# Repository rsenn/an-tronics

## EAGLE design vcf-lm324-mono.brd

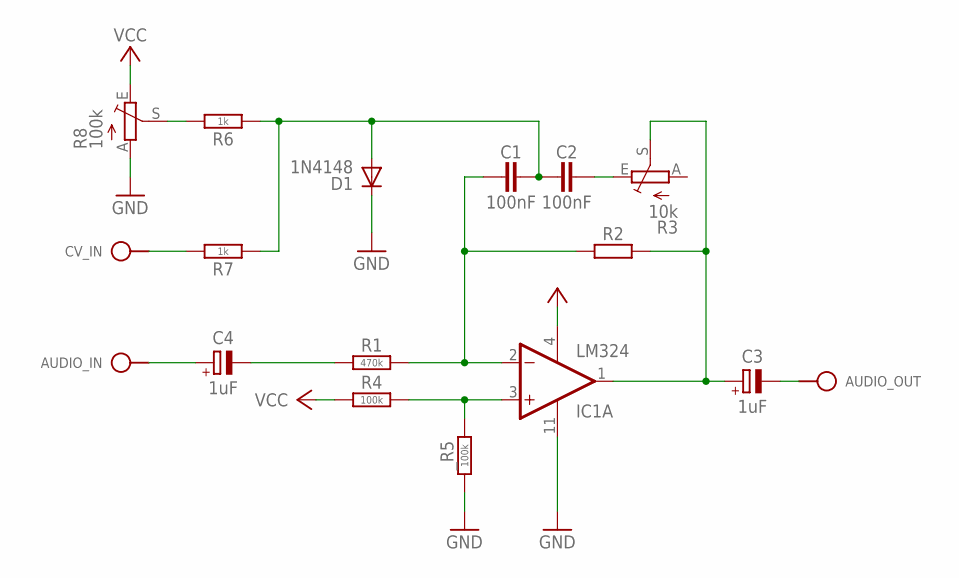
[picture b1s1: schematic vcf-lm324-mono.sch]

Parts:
AUDIO_IN: AUDIO_IN; SPAD
AUDIO_OUT: AUDIO_OUT; SPAD
C1, C2: 100nF; C050-024X044
C3, C4: 1uF; E2,5-3
CV_IN: CV_IN; SPAD
D1: 1N4148; DO34-7
IC1: LM324; DIL14
R1: 470k; 0202/7
R2: R0202/7; 0202/7
R3: 10k; RJ9W
R4: 100k; 0202/7
R6, R7: 1k; 0202/7
R8: 100k; RJ9W
_R5: 100k; 0202/7

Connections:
GND: D1.C, IC1.11 (V-), R8.A, _R5.1
unnamed: AUDIO_IN.1, C4.+
unnamed: C1.1, IC1.2 (-IN), R1.2, R2.1
unnamed: C2.2, R3.E
unnamed: C3.+, IC1.1 (OUT), R2.2, R3.S
unnamed: R6.2, R8.S
unnamed: AUDIO_OUT.1, C3.-
unnamed: IC1.3 (+IN), R4.2, _R5.2
unnamed: CV_IN.1, R7.2
unnamed: C1.2, C2.1, D1.A, R6.1, R7.1
unnamed: C4.-, R1.1
VCC: IC1.4 (V+), R4.1, R8.E

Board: 2 copper layers, 17 parts (0 on the bottom side), 12 nets, no tracks yet.

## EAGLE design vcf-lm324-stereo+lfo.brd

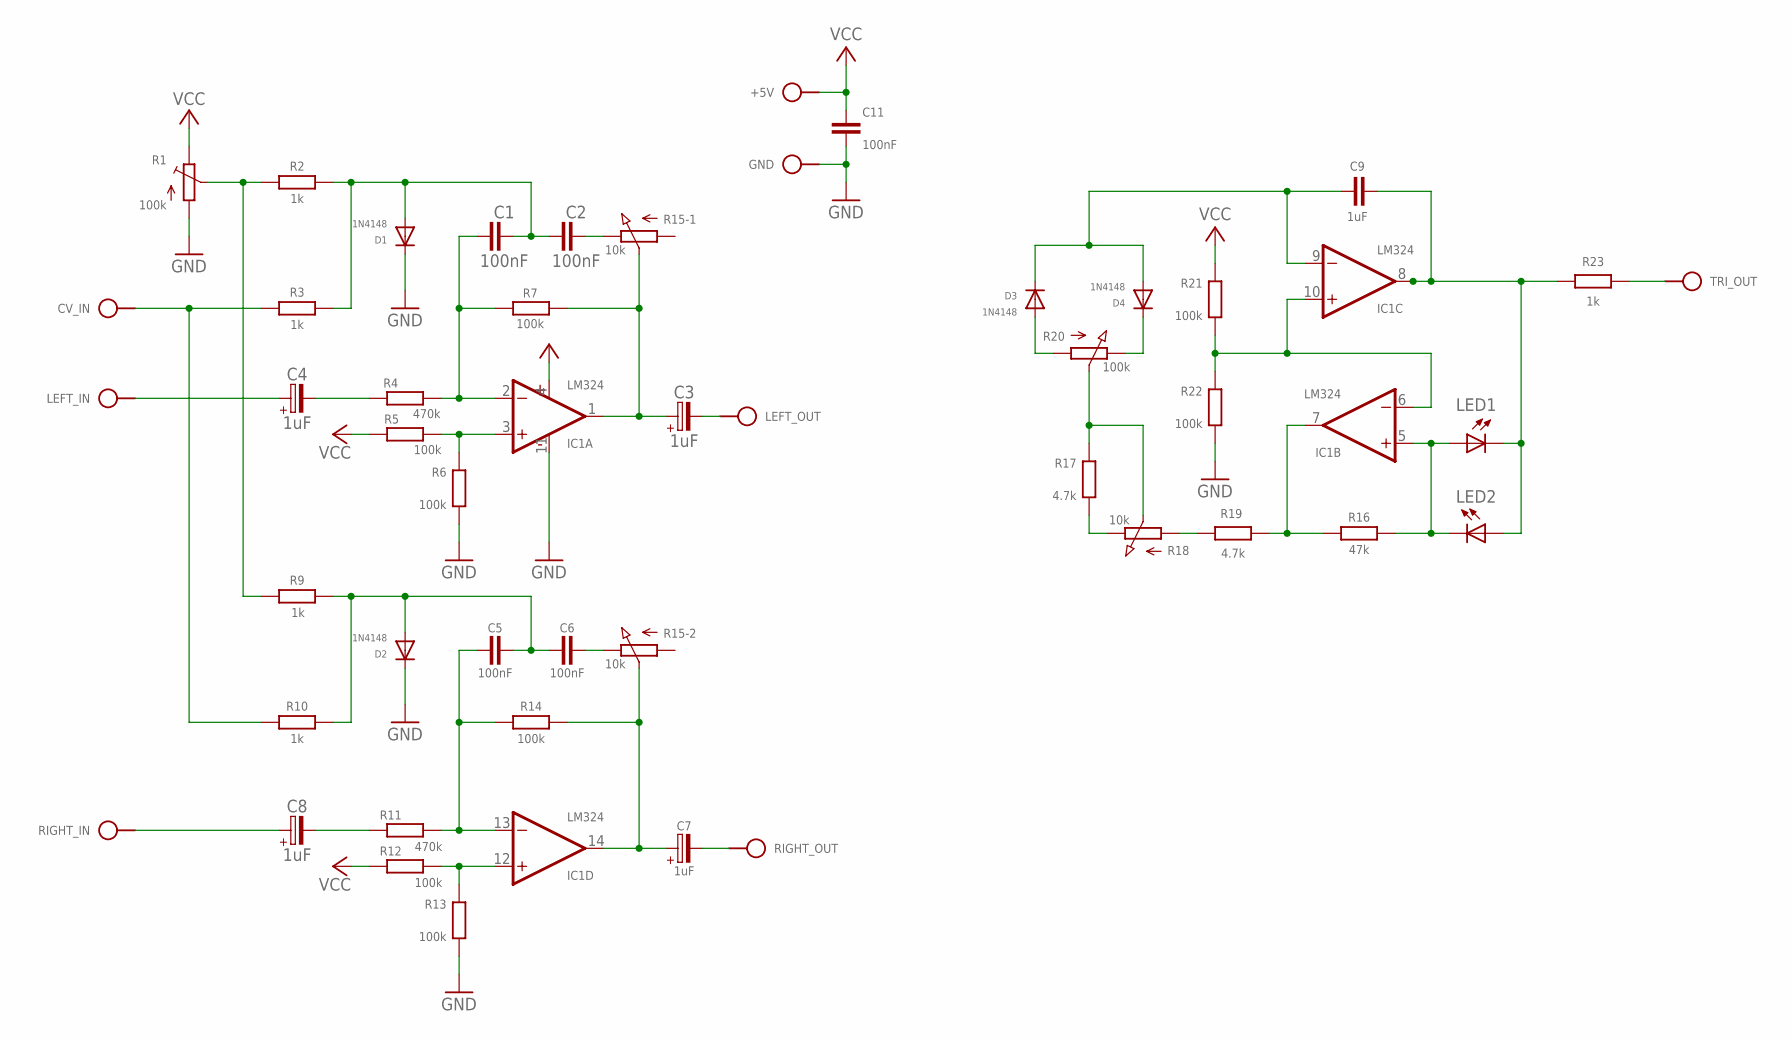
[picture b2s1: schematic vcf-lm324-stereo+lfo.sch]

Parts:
+5V: VCC; SPAD
C1, C2, C5, C6: 100nF; C050-024X044
C3, C4, C7, C8: 1uF; E2,5-3
C9: 1uF; C050-024X044/V
C11: 100nF; C050-020X036
CV_IN: CV_IN; SPAD
D1: 1N4148; DO34-10V
D2, D3, D4: 1N4148; DO34-7V
GND: GND; SPAD
IC1: LM324; DIL14
LED1, LED2: LED3MM
LEFT_IN: AUDIO_IN; SPAD
LEFT_OUT: AUDIO_OUT; SPAD
R1: 100k; B64Y
R2, R3, R9: 1k; 0202/7
R4, R11: 470k; 0202/7
R5, R6, R7: 100k; 0202/7
R10: 1k; 0202/5
R12, R14: 100k; 0202/5
R13: 100k; 0202V
R15: 10k; POT-STEREO
R16: 47k; 0202/7-V
R17: 4.7k; 0202/7
R18: 10k; POT
R19: 4.7k; 0202/7-V
R20: 100k; POT
R21, R22: 100k; 0202/7-V
R23: 1k; 0202/7-V
RIGHT_IN: AUDIO_IN; SPAD
RIGHT_OUT: AUDIO_OUT; SPAD
TRI_OUT: TRIANGLE; SPAD

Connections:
GND: C11.2, D1.C, D2.C, GND.1, IC1.11 (V-), R1.A, R6.1, R13.1, R22.1
unnamed: C4.+, LEFT_IN.1
unnamed: C1.1, IC1.2 (-IN), R4.2, R7.1
unnamed: C2.2, R15.1-3 (E)
unnamed: C3.+, IC1.1 (OUT), R7.2, R15.1-2 (S)
unnamed: R1.S, R2.2, R9.2
unnamed: C3.-, LEFT_OUT.1
unnamed: IC1.3 (+IN), R5.2, R6.2
unnamed: CV_IN.1, R3.2, R10.2
unnamed: C1.2, C2.1, D1.A, R2.1, R3.1
unnamed: C4.-, R4.1
unnamed: C6.2, R15.2-3 (E)
unnamed: C7.+, IC1.14 (OUT), R14.2, R15.2-2 (S)
unnamed: IC1.12 (+IN), R12.2, R13.2
unnamed: IC1.7 (OUT), R16.2, R19.1
unnamed: IC1.5 (+IN), LED1.A, LED2.K (C), R16.1
unnamed: C5.2, C6.1, D2.A, R9.1, R10.1
unnamed: C5.1, IC1.13 (-IN), R11.2, R14.1
unnamed: C7.-, RIGHT_OUT.1
unnamed: C8.+, RIGHT_IN.1
unnamed: C8.-, R11.1
unnamed: C9.1, D3.C, D4.A, IC1.9 (-IN)
unnamed: C9.2, IC1.8 (OUT), LED1.K (C), LED2.A, R23.2
OA_C_IN+: IC1.6 (-IN), IC1.10 (+IN), R21.1, R22.2
TRIM_1_A: D3.A, R20.1 (A)
TRIM_1_B: D4.C, R20.3 (E)
TRIM_2_A: R17.1, R18.3 (E)
TRIM_2_B: R18.1 (A), R19.2
TRIM_P: R17.2, R18.2 (S), R20.2 (S)
TRI_OUT: R23.1, TRI_OUT.1
VCC: +5V.1, C11.1, IC1.4 (V+), R1.E, R5.1, R12.1, R21.2

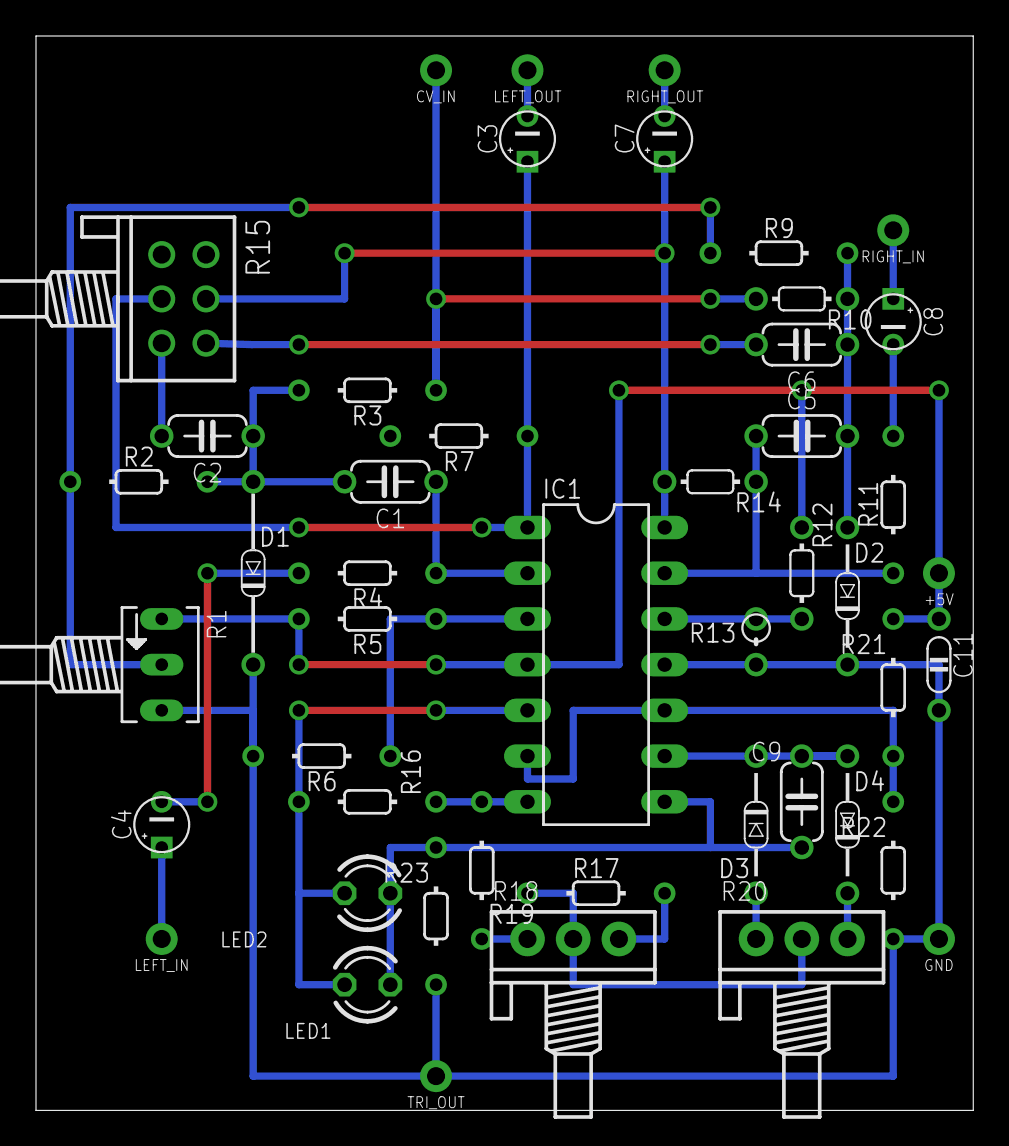
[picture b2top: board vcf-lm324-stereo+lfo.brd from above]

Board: 2 copper layers, 52.1 x 59.7 mm, 47 parts (0 on the bottom side), 31 nets.

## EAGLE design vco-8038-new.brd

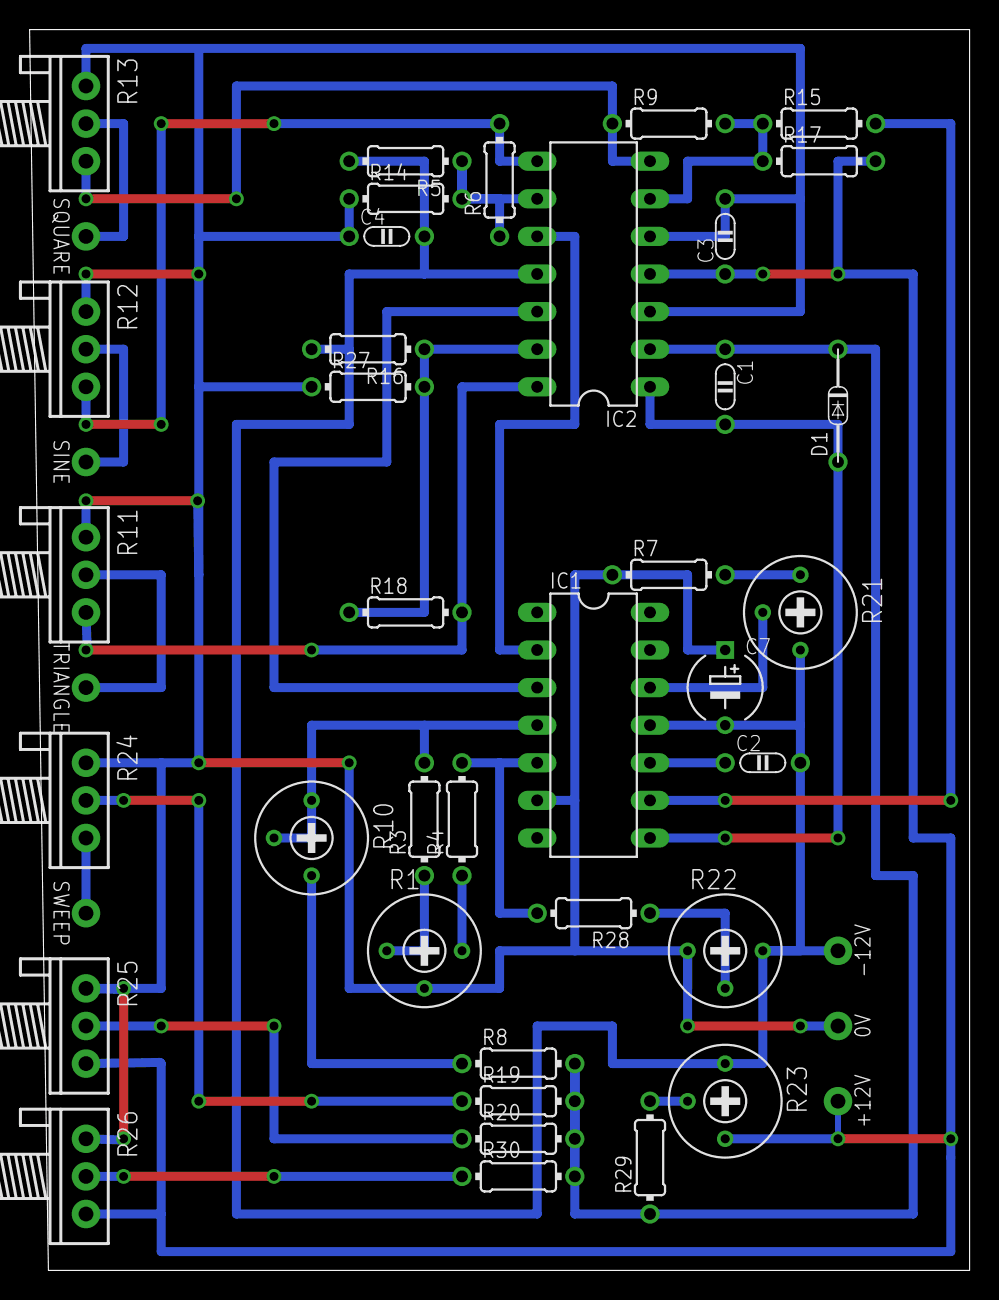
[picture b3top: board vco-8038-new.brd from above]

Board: 2 copper layers, 63.5 x 83.8 mm, 44 parts (0 on the bottom side), 31 nets.

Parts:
0V: SPAD
+12V: SPAD
-12V: SPAD
C1: 1nF; C050-020X036
C2: 4.7nF; C050-020X036
C3, C4: 10nF; C050-020X036
C7: 4.7uF; E5-5/V
D1: 1N4148; DO34-7
IC1: ICL8038; DIL14
IC2: TL074; DIL14
R1: 1k; R-TRIM
R3, R4: 1.5k; 0204/7
R5, R17: 5.6k; 0204/7
R6, R7, R8, R9: 10k; 0204/7
R10: 10k; R-TRIM
R11, R12, R13: 10k; POT
R14, R15: 12k; 0204/7
R16: 24k; 0204/7
R18: 30k; 0204/7
R19, R20: 100k; 0204/7
R21, R22, R23: 100k; R-TRIM
R24, R25, R26: 100k; POT
R27: 120k; 0204/7
R28: 470k; 0204/7
R29, R30: 10M; 0204/7
SINE: SPAD
SQUARE: SPAD
SWEEP: SPAD
TRIANGLE: SPAD

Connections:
GND: 0V.1, C3.2, C4.1, C7.+, IC1.6, IC2.3, IC2.5, R1.2, R7.1, R11.1, R12.1, R13.1, R14.1, R22.1, R24.1, R25.1, R26.1, R27.1
LF_SYMM: R22.2, R28.1
unnamed: R23.2, R29.2
unnamed: C1.2, D1.A, IC1.8, IC2.1
unnamed: C1.1, D1.C, IC2.2, R8.2, R19.2, R20.2, R29.1, R30.2
unnamed: R26.2, R30.1
unnamed: R20.1, R25.2
unnamed: R19.1, R24.2
unnamed: R24.3, SWEEP.1
unnamed: R8.1, R10.3
unnamed: R1.1, R3.1
unnamed: R1.3, R4.1
unnamed: IC1.4, R3.2, R10.1, R10.2
unnamed: IC2.13, R16.1, R18.1, R27.2
unnamed: IC1.5, R4.2, R28.2
unnamed: IC2.14, R11.3, R18.2
unnamed: R11.2, TRIANGLE.1
unnamed: IC1.3, IC2.12
unnamed: IC2.9, R5.1, R6.1, R14.2
unnamed: IC2.8, R6.2, R12.3
unnamed: R12.2, SINE.1
unnamed: IC1.2, IC2.10
unnamed: R7.2, R21.1
unnamed: IC1.12, R21.2
unnamed: C2.1, IC1.10
unnamed: IC2.6, R9.2, R15.1, R17.1
unnamed: IC2.7, R9.1, R13.3
unnamed: R13.2, SQUARE.1
unnamed: IC1.9, R15.2
V+: +12V.1, C3.1, IC2.4, R17.2, R23.3, R25.3, R26.3
V-: -12V.1, C2.2, C4.2, C7.-, IC1.11, IC2.11, R5.2, R16.2, R21.3, R22.3, R23.1
